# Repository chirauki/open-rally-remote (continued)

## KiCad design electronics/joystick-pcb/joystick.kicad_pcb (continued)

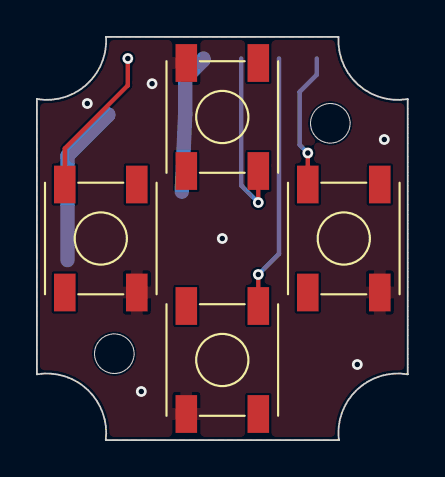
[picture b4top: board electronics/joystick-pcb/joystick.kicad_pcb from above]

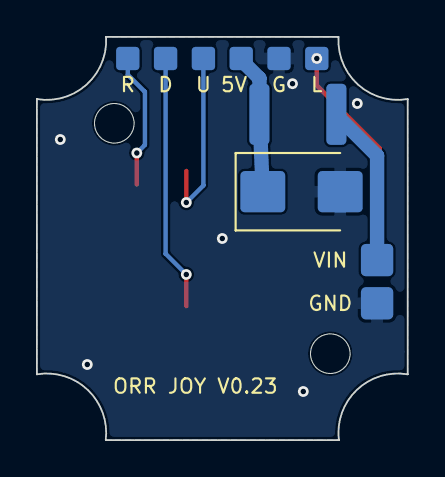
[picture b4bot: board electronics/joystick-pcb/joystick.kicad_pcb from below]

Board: 2 copper layers, 20.6 x 22.4 mm, 10 parts (4 on the bottom side), 7 nets.

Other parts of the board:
H1, H2: M2 standoff; Standoff_M2_PCB

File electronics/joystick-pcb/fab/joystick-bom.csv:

"Reference","Value","Footprint","Manufacturer","MPN","LCSC","Qty"
"D1","SMBJ5.0A","Diode_SMD:D_SMB","Littelfuse","SMBJ5.0A","C83333","1"
"F1","MF-MSMF050-2","Fuse:Fuse_1812_4532Metric","Bourns","MF-MSMF050-2","C17313","1"
"SW1-SW4","KSC221JLFS","orr:KSC2_SMD_6.2x6.2mm","C&K","KSC221JLFS","C221726","4"

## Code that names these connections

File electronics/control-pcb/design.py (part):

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             "R2", "R3", "R4", "R5", "R6", "R7", "C5", "J1", "J2", "J4", "SW1", "SW2", "SW3"]
PWR_FLAG_NETS = ["GND", "/VBUS", "/VBUS_IN", "/BAT"]
SCH_NOTE = ("Power: USB-C VBUS_IN -> F1 -> VBUS (D1 clamps) -> U1 MCP73831 charger, 100 mA (R1).\n"
            "Battery: J5 -> Q1 (reverse polarity) -> BAT_SYS -> U2 TPS70933 -> +3V3 -> XIAO 3V3 pin.\n"
            "Sense: BAT_SYS / 2 -> D0 (A0); STAT x 2/3 -> D8 (high when charging is done); VBUS x 2/3 -> D9.\n"
            "STAT also sinks the charge LED on the USB-C board (J3 pin 3), lit only while charging.\n"
            "XIAO headers J1 (D0-D6) and J2 (5V, GND, 3V3, D10, D9, D8, D7); 5V and D10 open.")

# --- Outline (matches ctrl_pcb_y, ctrl_pcb_clear and the upper cover bosses in the CAD) --
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
TEXTS = [
    ("ORR CONTROL V0.26", 0.0, -11.0, "F", 0.8),
    # Battery polarity at J5 (pin 1 BAT at x = -3.8, pin 2 GND at x = -5.8), on the rear
    # beyond its courtyard toward the board's end (F1 is on the other side), so a builder can
    # check the pouch plug before plugging it in.
    ("+", -3.8, -21.0, "B", 1.0),
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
